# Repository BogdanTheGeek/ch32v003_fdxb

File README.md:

FDX-B Pet Microchip Reader based on the ch32v003.

# Hardware
The reader coil should be about 5cm in diameter.
Around 50 turns should be enough.

You should aim for an inductance between 400uH to 1mH and a Q of around 8.
Check the Microchip application note in /docs.

The circuit is quite simple, all of the elements are clearly labled in the schematic.

I have included a schematic dedicated for simulating the circuit.

The PCB was designed to be easly for me to etch at home.

# Firmware

## Build
```sh
cd firmware
git submodule update --init --recursive --depth=1
make
```

Alternatively you can define a env variable with the path to your local `ch32fun`:
```sh
export CH32V003FUN=~/ch32fun/ch32fun
```

## How does it work
Timer 1 is used to produce a driving signal for the mosfets that includes deadtime.
An external interrupt is generated on each edge of the signal and this is where most of the decoding happens.

The signal is ecoded with Biphase encoding, meaning that 2 short consecutive periods between signal edges represent a 0 and one longer period represents a 1.

The code uses 2 buffers of 128bits (as 4 x 32bit), one is the working buffer and the other contains the last decoded frame.

Detected bits are loaded from the least significant bit to the most significant bit. The current bit index and a bit mask is used to compare the current state of the buffer to the start condition (1 followed by exactly 10 zeros) as well as to check the control bits. If at any point the buffer doesn't match the expected bit pattern, the bit count and the mask are reset.

Once the working buffer is full, we swap buffers.
We can then parse the raw bit pattern into a struct.

A bunch of optimisations have been made to ensure that the code is as small as possible, but still pretty fast.
Most comparison values have been calculated at compile time and all necesery divisions and modulo opperations have been implemented using bit shifts and bitwise ANDs.

The CRC16K is calculated and verified during the parsing of the bit pattern to minimise copies.

I have included a function that can print a `uint64_t` integer with 0 padding without the use of any decimal division/modulus instructions (which would add about 3k to the binary)

With logs off (but still printing an ID):
```
  FLASH:        2592 B        16 KB     15.82%
    RAM:          60 B         2 KB      2.93%
```

# Resources
 - Nice description of the protocol: https://www.priority1design.com.au/fdx-b_animal_identification_protocol.html
 - Similar project base on Arduino: https://github.com/decrazyo/fdxb
 - FDX-B decoder for sigrok: https://github.com/swdee/fdx-b-decoder

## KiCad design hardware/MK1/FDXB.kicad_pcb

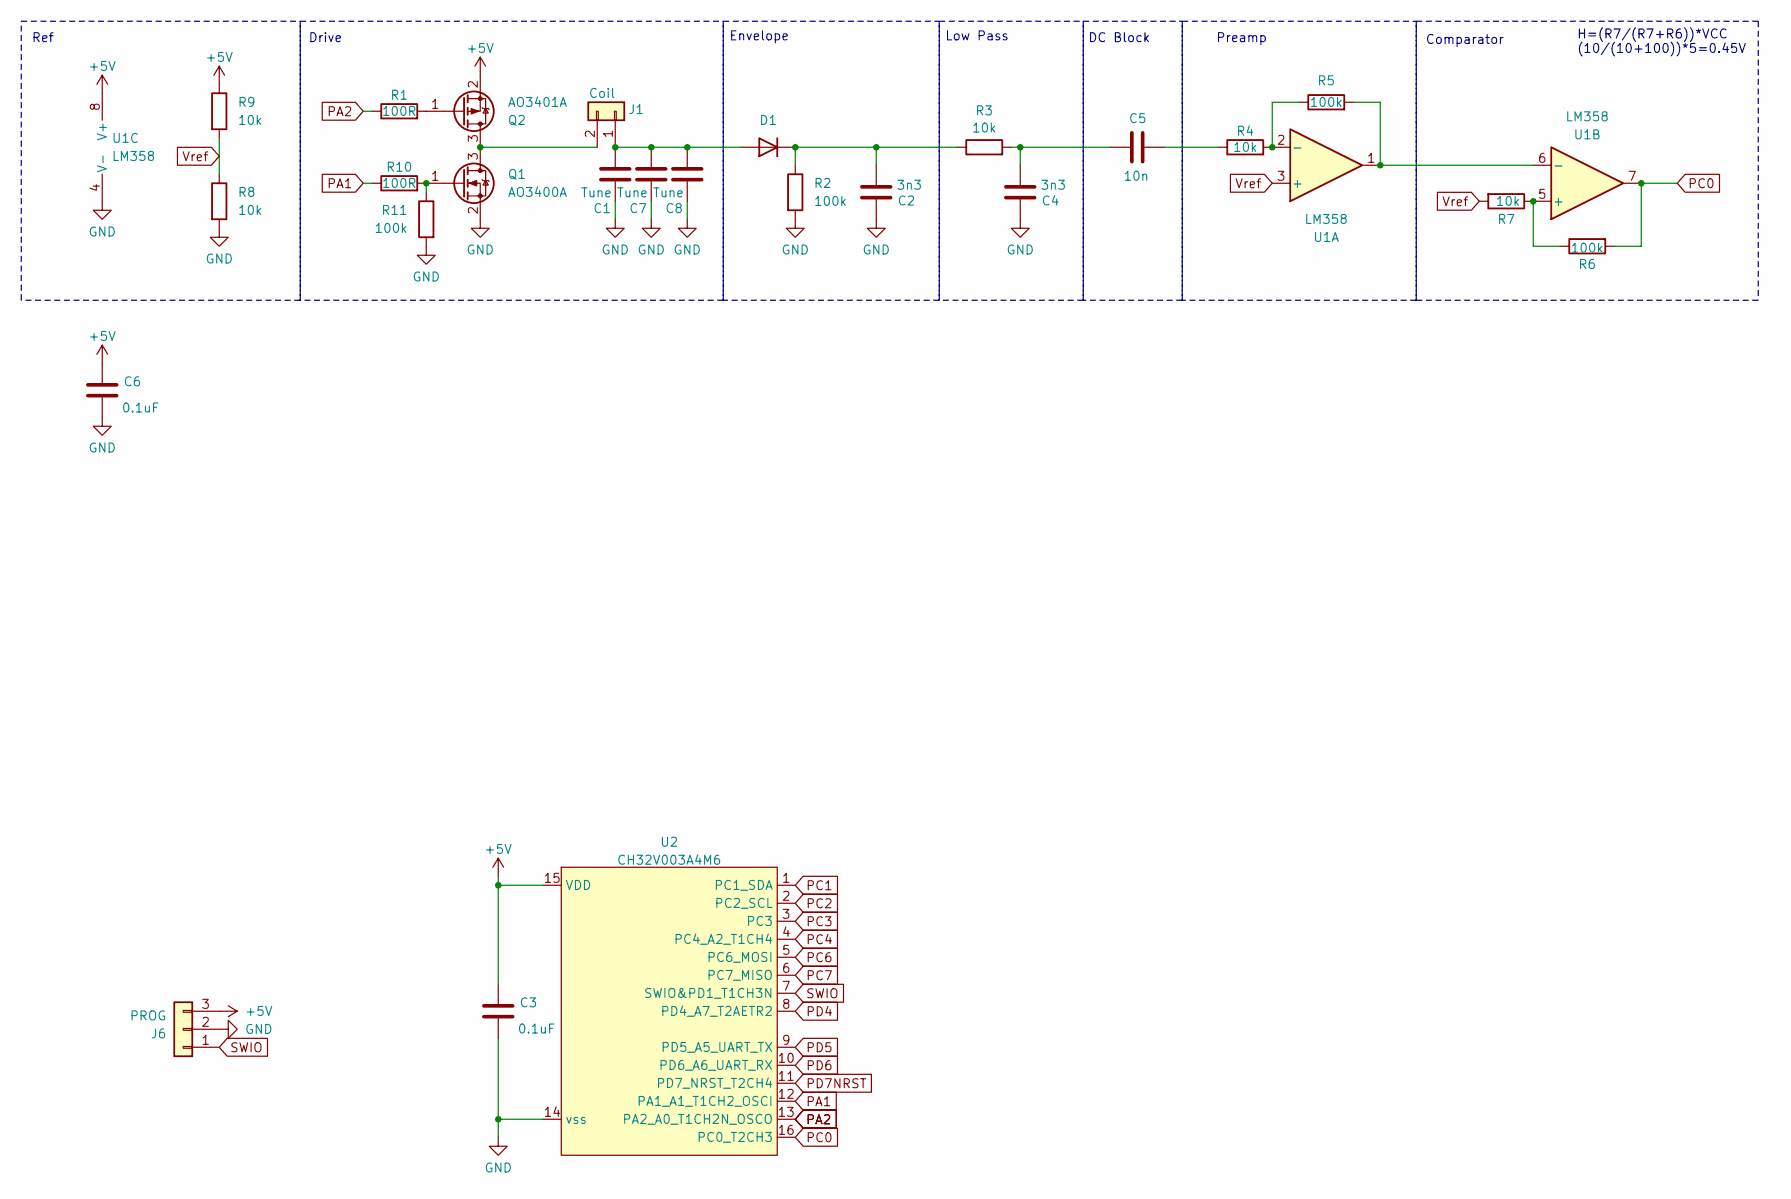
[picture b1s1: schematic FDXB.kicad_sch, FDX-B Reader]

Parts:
C1, C7, C8: Tune; C_0603_1608Metric_Pad1.08x0.95mm_HandSolder
C2, C4: 3n3; C_0603_1608Metric_Pad1.08x0.95mm_HandSolder
C3, C6: 0.1uF; C_0603_1608Metric_Pad1.08x0.95mm_HandSolder
C5: 10n; C_0603_1608Metric_Pad1.08x0.95mm_HandSolder
D1: D; D_SMA
J1: Coil; PinSocket_1x02_P2.54mm_Vertical
J6: PROG; PinHeader_1x03_P2.54mm_Vertical
Q1: AO3400A; SOT-23
Q2: AO3401A; SOT-23
R1, R10: 100R; R_1206_3216Metric
R2, R5, R6, R11: 100k; R_1206_3216Metric
R3, R4, R7, R8, R9: 10k; R_1206_3216Metric
U1: LM358; SOIC-8_3.9x4.9mm_P1.27mm
U2: CH32V003A4M6; SO-16_3.9x9.9mm_P1.27mm

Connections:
+5V: C3.1, C6.1, J6.3, Q2.2 (S), R9.1, U1.8 (V+), U2.15 (VDD)
GND: C1.1, C2.1, C3.2, C4.1, C6.2, C7.1, C8.1, J6.2, Q1.2 (S), R2.2, R8.2, R11.2, U1.4 (V-), U2.14 (vss)
unnamed: C4.2, C5.2, R3.2
unnamed: C5.1, R4.1
unnamed: C1.2, C7.2, C8.2, D1.2 (A), J1.1
unnamed: C2.2, D1.1 (K), R2.1, R3.1
unnamed: J1.2, Q1.3 (D), Q2.3 (D)
unnamed: Q1.1 (G), R10.2, R11.1
unnamed: Q2.1 (G), R1.2
unnamed: R4.2, R5.1, U1.2 (-)
unnamed: R6.1, R7.1, U1.5 (+)
unnamed: R5.2, U1.1, U1.6 (-)
PA1: R10.1, U2.12 (PA1_A1_T1CH2_OSCI)
PA2: R1.1, U2.13 (PA2_A0_T1CH2N_OSCO)
PC0: R6.2, U1.7, U2.16 (PC0_T2CH3)
PC1: U2.1 (PC1_SDA)
PC2: U2.2 (PC2_SCL)
PC3: U2.3 (PC3)
PC4: U2.4 (PC4_A2_T1CH4)
PC6: U2.5 (PC6_MOSI)
PC7: U2.6 (PC7_MISO)
PD4: U2.8 (PD4_A7_T2AETR2)
PD5: U2.9 (PD5_A5_UART_TX)
PD6: U2.10 (PD6_A6_UART_RX)
PD7NRST: U2.11 (PD7_NRST_T2CH4)
SWIO: J6.1, U2.7 (SWIO&PD1_T1CH3N)
Vref: R7.2, R8.1, R9.2, U1.3 (+)

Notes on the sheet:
H=(R7/(R7+R6))*VCC (10/(10+100))*5=0.45V
Drive
Preamp
Envelope
Ref
DC Block
Comparator
Low Pass

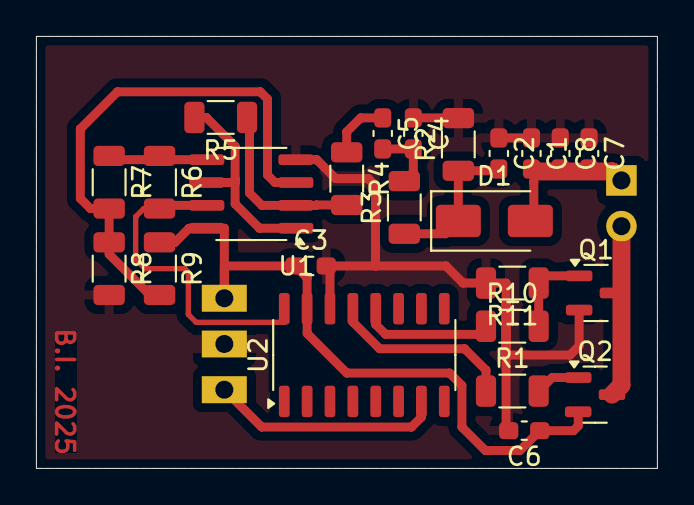
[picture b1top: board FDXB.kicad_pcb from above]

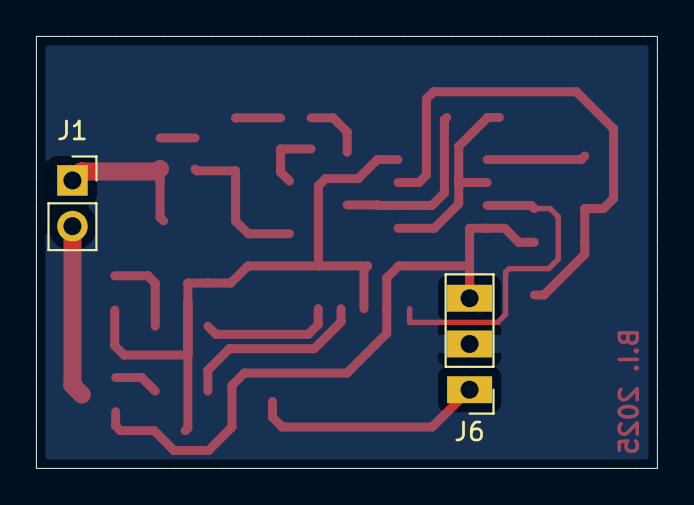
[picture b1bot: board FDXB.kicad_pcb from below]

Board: 2 copper layers, 34.5 x 24.0 mm, 26 parts (2 on the bottom side), 17 nets.

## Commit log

2025-03-24 working and optimised
2025-03-24 add images
